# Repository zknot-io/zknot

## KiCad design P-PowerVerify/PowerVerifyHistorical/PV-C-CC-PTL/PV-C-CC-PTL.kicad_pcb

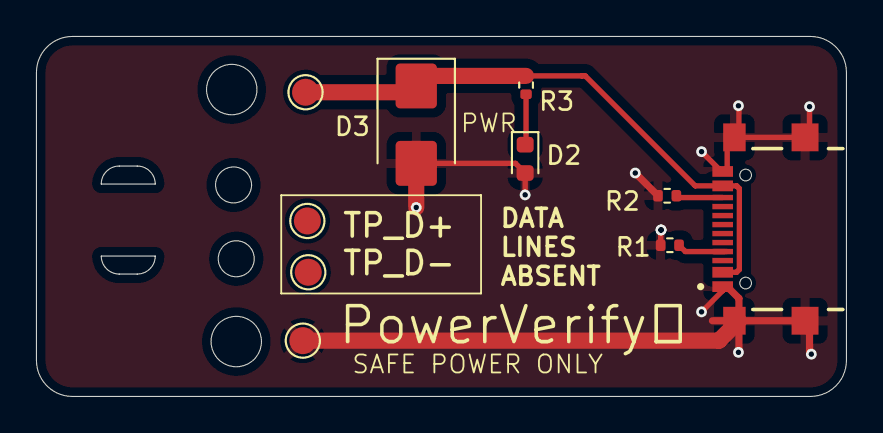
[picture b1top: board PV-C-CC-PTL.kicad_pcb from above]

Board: 2 copper layers, 45.0 x 20.0 mm, 10 parts (0 on the bottom side), 5 nets.

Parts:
D2: LED; LED_0603_1608Metric
D3: SMBJ5.0A; D_SMB
J1: USB_C_Receptacle_USB2.0_16P; GCT_USB4216-03-A_REVA
R1, R2: 5.1k; R_0402_1005Metric
R3: 470ohm; R_0402_1005Metric
TP1, TP2, TP3, TP4: TestPoint; TestPoint_Pad_D1.5mm

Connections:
/CC1: J1.A5 (CC1), R1.2
/CC2: J1.B5 (CC2), R2.2
/GND: D2.2 (A), D3.2 (A2), J1.A1_B12, J1.B1_A12, J1.SH1, J1.SH2, J1.SH3, J1.SH4, R1.1, R2.1, TP4.1
/VBUS: D3.1 (A1), J1.A4_B9, J1.B4_A9, R3.2, TP3.1
unnamed: D2.1 (K), R3.1

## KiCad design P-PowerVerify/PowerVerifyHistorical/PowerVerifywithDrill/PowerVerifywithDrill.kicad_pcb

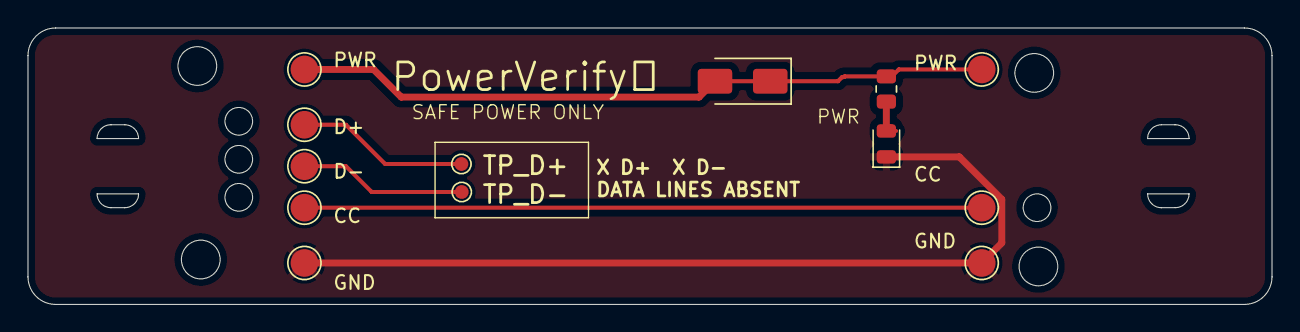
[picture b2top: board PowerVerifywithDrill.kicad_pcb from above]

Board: 2 copper layers, 90.0 x 20.0 mm, 13 parts (0 on the bottom side), 4 nets.

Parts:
D1: LED GREEN; LED_0805_2012Metric
D3: D_TVS; D_SMA
R3: 1k; R_0805_2012Metric
TP1: TP_DPLUS; TestPoint_Pad_D1.0mm
TP2: TP_DMINUS; TestPoint_Pad_D1.0mm
TP3, TP4, TP5, TP6, TP7, TP8, TP9, TP10: TestPoint; TestPoint_Pad_D2.0mm

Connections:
GND: D1.1 (K), TP7.1, TP8.1
unnamed: D1.2 (A), R3.1
unnamed: TP4.1, TP9.1
VBUS: D3.1 (A1), D3.2 (A2), R3.2, TP3.1, TP10.1
